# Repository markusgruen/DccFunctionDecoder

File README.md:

# DccFunctionDecoder

Hier klicken für deutsch: [Deutsche Doku](https://github.com/markusgruen/DccFunctionDecoder/blob/main/README_DE.md)

---

A simple DCC function decoder with 4 AUX channels. Compiles for an ATtiny402

Functionality:
- CV configurable
- 4 individual outputs
- 3 modes available for each output: FADE, BLINK, NEON
- Function mapping for F0...F20 for each output
- short and long address
- consist address

## Hardware
KiCad files are available in the `Hardware`-folder

The PCB has a size of approx. 7 by 7 mm. PCB is double-sided and only has standard components in the size of 0603 or larger to enable hand soldering of the decoder.

## Software
The software can be compiled and flashed using the Arduino environment.

## Usage
### Flashing the software
You will require a standard USB-UART adapter (5V compatible). Connect the adapter as shown with the decoder. You **MUST NOT** connect the decoder's 5V with the UART-adapter. The LDO on the decoder does not like being reverse powered. Switch on the rail's power supply.

Select the appropriate COM port in the Arduino IDE and select `Sketch -> Upload using Programmer` (or hit **CTRL+SHIFT+U**). Just hitting the `Upload`-Button (or pressing **CTRL+U**) will not work.

### First usage of the decoder after flashing
Right after flashing, the Decoder is NOT yet ready for usage, as the ATtiny's EEPROM is still on factory default and the decoder therefore has an unknown address. You can already wire up the decoder as described in the following section. Then, perform a factory reset of the decoder by writing the value 8 to CV8, using the decoder's magic address 10239. In case you forgot your decoder's address, you can always perform CV writes using the magic address 10239. If you are using DecoderPro, proceed as shown below: 

### Using the decoder in a locomotive or wagon
Connect the LEDs as shown. Use appropriate resistors. The maximum current should be limited to 2 mA per LED. That does sound little but usually it is enough. Otherwise the LDO on the decoder gets too hot. 

### Programming CVs
The decoder ONLY supports Programming on Main (POM) mode. It cannot generate an ACK. For CVs see the following table below. The decoder will confirm each CV write with a short flash of all AUX channels. 

#### Programming the address
Special note on programming the address: If you want to change the decoder's address, you must do so in the following order:
1. program CV3 or CV17 and CV18 as desired.
2. program CV29 = 0 (short address) or CV29 = 32 (long address)

From then on, the decoder will only accept CV writes or commands to the new address. (it will of course still accept commands to its consist address)

#### Decoder reset
The decoder can be reset to its default CV values by writing CV8 = 8. This is confirmed by multiple short flashes of all AUX channels.

#### CV table

| CV | Type | range | default Value | Description |
|----------|----------|----------|----------|----------|
| 1 | address | 1...127 | 3 | short address |
| 17 | long Address high byte | 192...255 | 195 | CV17 = 192 + (address / 256) |
| 18 | long address low byte  | 0...255   | 232 | CV18 = address mod 256 |
| 19 | consist address  | 0...255   | 0 | consist address |
| 29 | configuration byte  | 0...255   | 0 | CV29 = 0: short address;<br>CV29 = 32: long address |
| 33...35<br>36...38<br>39...41<br>42...44 | FunctionMap AUX n <br> (3 bytes for each AUX. The 3 bytes form a "word" with 24 bits)  | each CV: 0...255  | CV33 = 0b00000010 (F1) <br> CV36 = 0b00000100 (F2) <br> CV39 = 0b00001000 (F3) <br> CV42 = 0b00010000 (F4) <br> all others = 0  | Bit 0 = 1: AUX n controlled by F0<br> Bit 1 = 1: AUX n controlled by F1 <br>...<br> Bit 20 = 1 : AUX n controlled by F20 <br> Bit 21: reserved <br> Bit 22 = 1: AUX n only active when forward <br> Bit 23 = 1: AUX n only active when reverse |
| 57 <br> 58 <br> 59 <br> 60  | Output mode AUX n  | 0...2   |   0 | 0 = fade <br> 1 = neon <br> 2 = Blink |
| 65 <br> 66 <br> 67 <br> 68  | dimm value AUX n   | 0...255 | 255 | 0 = off <br> ... <br> 255 = full brightness |
| 73 <br> 74 <br> 75 <br> 76  | fade speed AUX n   | 0...255 |   0 | 0 = instant on/off <br> ... <br> 255 = very slow fading |
| 97 <br> 98 <br> 99 <br> 100 | blink on time AUX n  | 0...255  |   80 | value * 10ms = on-time during blink <br> (only active when CV57...60 = 2) |
| 105 <br> 106 <br> 107 <br> 108 | blink off time AUX n  | 0...255  |   150 | value * 10ms = off-time during blink <br> (only active when CV57...60 = 2) |

## License and Legal
Copyright 2025 by Markus Grün

Software licensed under GNU General Public License v3.0, see license file in `Software`-folder

Hardware (Schematics, Layout, etc.) licensed under CERN-OHL-P v2 or later, see license file in `Hardware`-folder

THE SOFTWARE AND SOURCES ARE PROVIDED "AS IS", WITHOUT WARRANTY OF ANY KIND, EXPRESS OR IMPLIED, INCLUDING BUT NOT LIMITED TO THE WARRANTIES OF MERCHANTABILITY, FITNESS FOR A PARTICULAR PURPOSE AND NONINFRINGEMENT. IN NO EVENT SHALL THE AUTHORS OR COPYRIGHT HOLDERS BE LIABLE FOR ANY CLAIM, DAMAGES OR OTHER LIABILITY, WHETHER IN AN ACTION OF CONTRACT, TORT OR OTHERWISE, ARISING FROM, OUT OF OR IN CONNECTION WITH THE SOFTWARE OR SOURCES OR THE USE OR OTHER DEALINGS IN THE SOFTWARE OR SOURCES.

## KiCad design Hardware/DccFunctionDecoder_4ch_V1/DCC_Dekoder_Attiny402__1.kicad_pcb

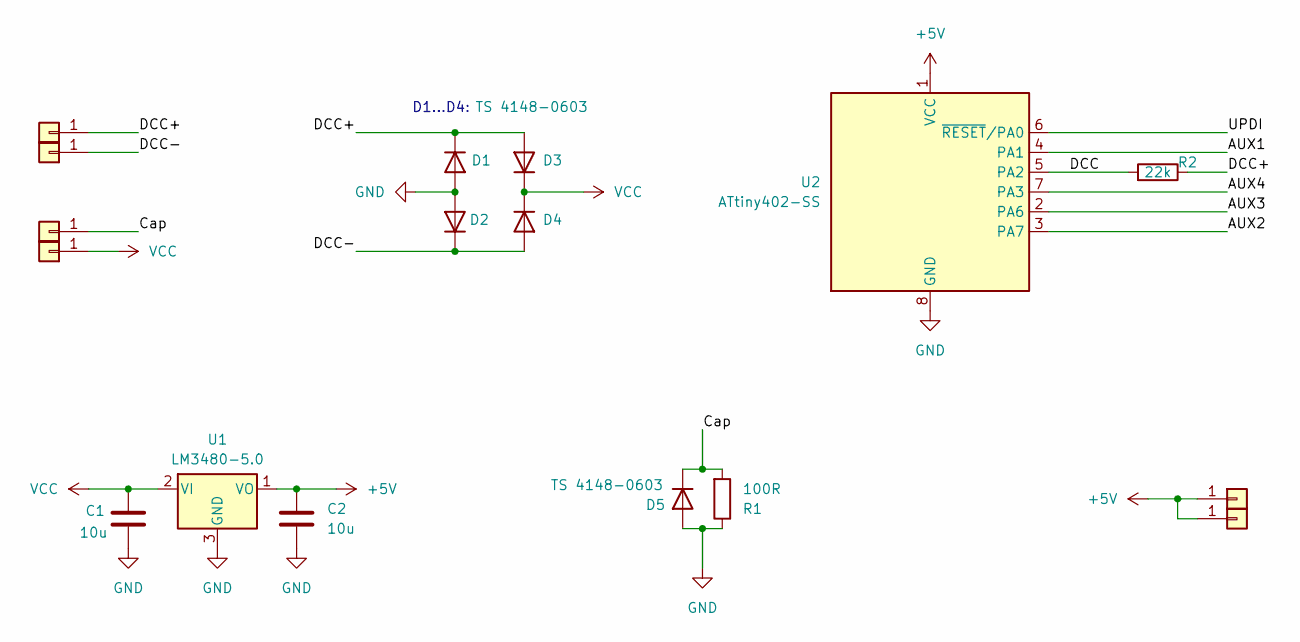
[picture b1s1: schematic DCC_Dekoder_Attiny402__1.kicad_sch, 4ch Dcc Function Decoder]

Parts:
C1, C2: 10u; C_0603_1608Metric_Pad1.08x0.95mm_HandSolder
D1, D2, D3, D4, D5: TS 4148-0603; D_0603_1608Metric_Pad1.05x0.95mm_HandSolder
J1, J2, J3, J4, J5, J7: Conn_01x01; Solderpad_1x_SMD_1.0x0.7
R1: 100R; R_0603_1608Metric_Pad0.98x0.95mm_HandSolder
R2: 22k; R_0603_1608Metric_Pad0.98x0.95mm_HandSolder
U1: LM3480-5.0; SOT-23
U2: ATtiny402-SS; SOIC-8_3.9x4.9mm_P1.27mm

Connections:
+5V: C2.1, J5.1, J7.1, U1.1 (VO), U2.1 (VCC)
/AUX1: U2.4 (PA1)
/AUX2: U2.3 (PA7)
/AUX3: U2.2 (PA6)
/AUX4: U2.7 (PA3)
/Cap: D5.1 (K), J2.1, R1.2
/DCC: R2.2, U2.5 (PA2)
/DCC+: D1.1 (K), D3.2 (A), J1.1, R2.1
/DCC-: D2.1 (K), D4.2 (A), J4.1
/UPDI: U2.6 (~RESET/PA0)
GND: C1.2, C2.2, D1.2 (A), D2.2 (A), D5.2 (A), R1.1, U1.3 (GND), U2.8 (GND)
VCC: C1.1, D3.1 (K), D4.1 (K), J3.1, U1.2 (VI)

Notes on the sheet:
D1...D4:

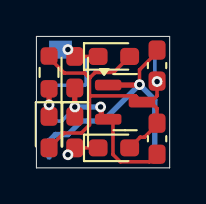
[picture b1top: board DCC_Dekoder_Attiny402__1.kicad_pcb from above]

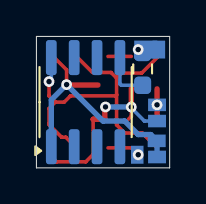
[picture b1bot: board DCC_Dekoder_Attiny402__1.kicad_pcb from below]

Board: 2 copper layers, 7.4 x 7.3 mm, 17 parts (8 on the bottom side), 7 nets.

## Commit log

2025-07-25 erster commit. Github hat mir geholfen den bitstream zu befüllen und angefangen ihn auszuwerten.
2025-07-27 DCC bitstream dekodieren klappt - was noch fehlt ist die XOR-Auswertung. im erzeugen des bitstreams aus Flankenwechseln ist noch ein chatgpt-Fehler. das muss ich noch manuell für den attiny machen. A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
2025-07-28 etwas weiter gemacht. kompiliert.
2025-07-29 getDirection und getFunctions verbessert. Kompiliert.
2025-07-29 mit functionOutputController angefangen, aber noch nicht weit
2025-07-30 weiter am functionOutputController geschrieben. ISR auf polling umgestellt <-- TODO: Am Mikrocontroller messen, wie lange die ISR dauert!
2025-08-04 Packethandler geändert auf polling mit Filter
2025-08-04 mitten im Funktionstest von functionOutputController. Schreiben der defaultCVs funktioniert. Soft-PWM funktioniert, Mapping der functions auf die CVs funktioniert (also das anschalten einer funktion 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
2025-08-05 fade funktioniert, blink noch nicht.
2025-08-06 blinken und faden geht jetzt. Lag an den Einstellungen für delay in den "tools". delay ist jetzt disabled.
2025-08-07 blinken jetzt mit getrennter on- und off Zeit. Außerdem Bug im SignalParser gefixt.
2025-08-07 etwas optimiert. als nächstes möchte ich ausprobieren, wieveil speicherplatz es bringt, wenn ich die Pins fest einprogrammiere.
2025-08-07 NEON passt jetzt gerade so auf den µC und funktioniert. Als nächstes: Klassen auflösen, alles global. Das sollte speicherplatz sparen. ggf. namespace nutzen.
2025-08-08 alle dcc-Dateien von Klasse auf Namespace geändert. Es kompiliert, ist aber noch nicht getestet.
2025-08-08 YES, 166 bytes gespart! und es geht noch mehr. jetzt functions in namespace verwandeln und dcc nochmals prüfen!
2025-08-15 Ich bin mittem im Test. SignalReceiver funktioniert nun. Da waren noch ein paar kleine Bugs. SignalParser funktioniert auch, allerdings sind die gelesenen Bits falsch rum (MSB first). Das könnte ich 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
2025-08-15 funktioniert leider noch nicht. ich finde den fehler nicht. Präambel wird erkannt, Byte wird auch korrekt gelesen, aber mit dem separator hakt es...
2025-08-15 YES, SignalParser funktioniert!!
2025-08-23 Schreiben von CVs wird nun per LED-blitz bestätigt. Wenn die Adresse geändert wird, wird sie im Decoder SOFORT geändert und er reagiert dann nur noch auf die neue Adresse.
    ACHTUNG - ACHTUNG - ACHTUNG:: das geht so nur mit kurzen adressen gut. Ich habe noch keine idee, wie ich lange adressen ändern kann?
2025-08-24 Adresse wird nun übernommen, wenn CV 29 geschrieben wird. - Achtung, kollidiert mit Decoder Pro, aber geht nicht anders.
2025-08-26 schon viel flash gespeichert. Teste gerade nochmal die neue outputcontroller.cpp. Leider klappt BLINK noch nicht.
2025-08-28 es sollte jetzt alles gehen. Getestet in stand-alone. Mit Gleis und DecoderPro geht es noch nicht. Muss ich noch debuggen.
2025-08-29 Kommandos von der DCC-Zentrale kommen richtig bis zum outputcontroller an, vPwmValue wird gesetzt (geprüft) aber in der ISR ist vPwmValue immer noch 0 ?!
2025-08-29 der Großteil geht jetzt tatsächlich. Nur NEON geht noch nicht, zumindest nicht das Wieder-Anschalten. Mir gefällt aber an sich der Code-Aufbau gar nicht gut. Das möchte ich nochmal ändern.
2025-08-29 Angefangen, den Code besser zu schreiben. FADE und BLINK gehen.
2025-08-30 jetzt funktioniert es FAST ! - musste vRtcOverflowcounter von 16bit auf 8 bit reduzieren. So konnte ich noch einiges an flash sparen. Allerdings klappt jetzt BLINK nicht mehr. Muss ich noch schauen w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
2025-08-31 so könnte es gehen, muss noch testen.
2025-08-31 Ja, jetzt gehts! Habe angefangen zu kommentieren.
2025-09-01 Kommentare ergänzt
2025-09-02 Release of V0.1
2025-09-03 Update README.md
    fix Function mapping only up to F20 in doku
2025-09-05 fix component values in schematics
2025-10-23 Bug in schematic for programming fixed (UART-GND now connects to Attiny-GND)
2025-10-26 Bugfix: added magic address that enables CV programming of a new processor.
2025-10-27 Note in ino-file added for "EEPROM retained"
2025-11-02 Bugfix: 1. Decoder now responds when placed either way on the tracks 2. Decoder only responds to addresses > 0
